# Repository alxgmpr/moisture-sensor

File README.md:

# moisture-sensor

A CR2032-powered Bluetooth soil-moisture sensor with two capacitive sensing zones. An FDC1004 capacitance-to-digital converter measures the probe, an Ezurio BL54L15 (nRF54L15) broadcasts BTHome v2 readings for Home Assistant, and an SHT40 adds temperature and humidity. Configuration and firmware updates happen over BLE.

**Status:** experimental prototype, firmware 0.2.28. SENSE2 shows a weaker response in soil than SENSE1 ([investigation](docs/sense2-investigation-2026-09-25.md)). Moisture percentages are relative to provisional dry/wet endpoints, and battery life and soil accuracy are not yet characterized.

## How it differs

**Y** = included in the device; **N** = not included. Connectivity reflects stock firmware (the BLE sample for b-parasite); other firmware or an external host can add capabilities.

| Feature | This project | [Seeed XIAO](https://wiki.seeedstudio.com/xiao_soil_moisture_sensor/) | [Adafruit STEMMA](https://www.adafruit.com/product/4026) | [Chirp!](https://wemakethings.net/chirp/) | [b-parasite](https://github.com/rbaron/b-parasite) |
| --- | :---: | :---: | :---: | :---: | :---: |
| Capacitive soil sensing | Y | Y | Y | Y | Y |
| Two independently read soil-sensing zones | Y | N | N | N | N |
| Dedicated capacitance-to-digital converter IC | Y | N | N | N | N |
| Operates without an additional controller | Y | Y | N | Y | Y |
| BLE moisture broadcasting in supplied firmware | Y | N | N | N | Y |
| Wi-Fi reporting in supplied firmware | N | Y | N | N | N |
| Onboard coin-cell power support | Y | N | N | Y | Y |
| Onboard AA battery power support | N | Y | N | N | N |
| Relative humidity measurement | Y | N | N | N | Y |
| Audible watering alarm | N | N | N | Y | N |

## Block diagram

```mermaid
flowchart LR
    BAT[CR2032] --> PMIC[nPM2100<br/>power management]
    PMIC --> MCU[BL54L15<br/>nRF54L15 + BLE]
    PMIC -- switched rail --> FDC[FDC1004<br/>capacitance-to-digital]
    FDC -- SENSE1 --- P1[Soil zone 1]
    FDC -- SENSE2 --- P2[Soil zone 2]
    FDC -- I²C --> MCU
    SHT[SHT40<br/>temp / humidity] -- I²C --> MCU
    MCU -- BTHome v2 / SMP --> HA[Home Assistant<br/>Web Bluetooth dashboard]
```

## Build

### Hardware

Open [nrf-moisture-sensor.kicad_pro](nrf-moisture-sensor.kicad_pro) in KiCad. The maintained schematic and PCB are authoritative. See the [BOM](BOM.md) and [design rationale](HARDWARE.md).

### Firmware

Requires Nordic nRF Connect SDK v3.2.2. From the repository root, in an SDK-configured environment:

```sh
west build --sysbuild -p always -b bl54l15_dvk/nrf54l15/cpuapp \
  -d firmware/sensor/build firmware/sensor
sh firmware/sensor/tests/run.sh
```

Wiring, signing, OTA, and SWD recovery are in the [sensor firmware guide](firmware/sensor/README.md). The SDK signing key is for development only.

### Browser configuration

```sh
node firmware/sensor/dashboard/serve.mjs
```

Open <http://127.0.0.1:8766> in Chrome or Edge. Connect during the sensor's advertising window, or use **Explore with demo data** without hardware. See the [dashboard guide](firmware/sensor/dashboard/README.md).

## Notes

Investigation records are in [docs/](docs/).

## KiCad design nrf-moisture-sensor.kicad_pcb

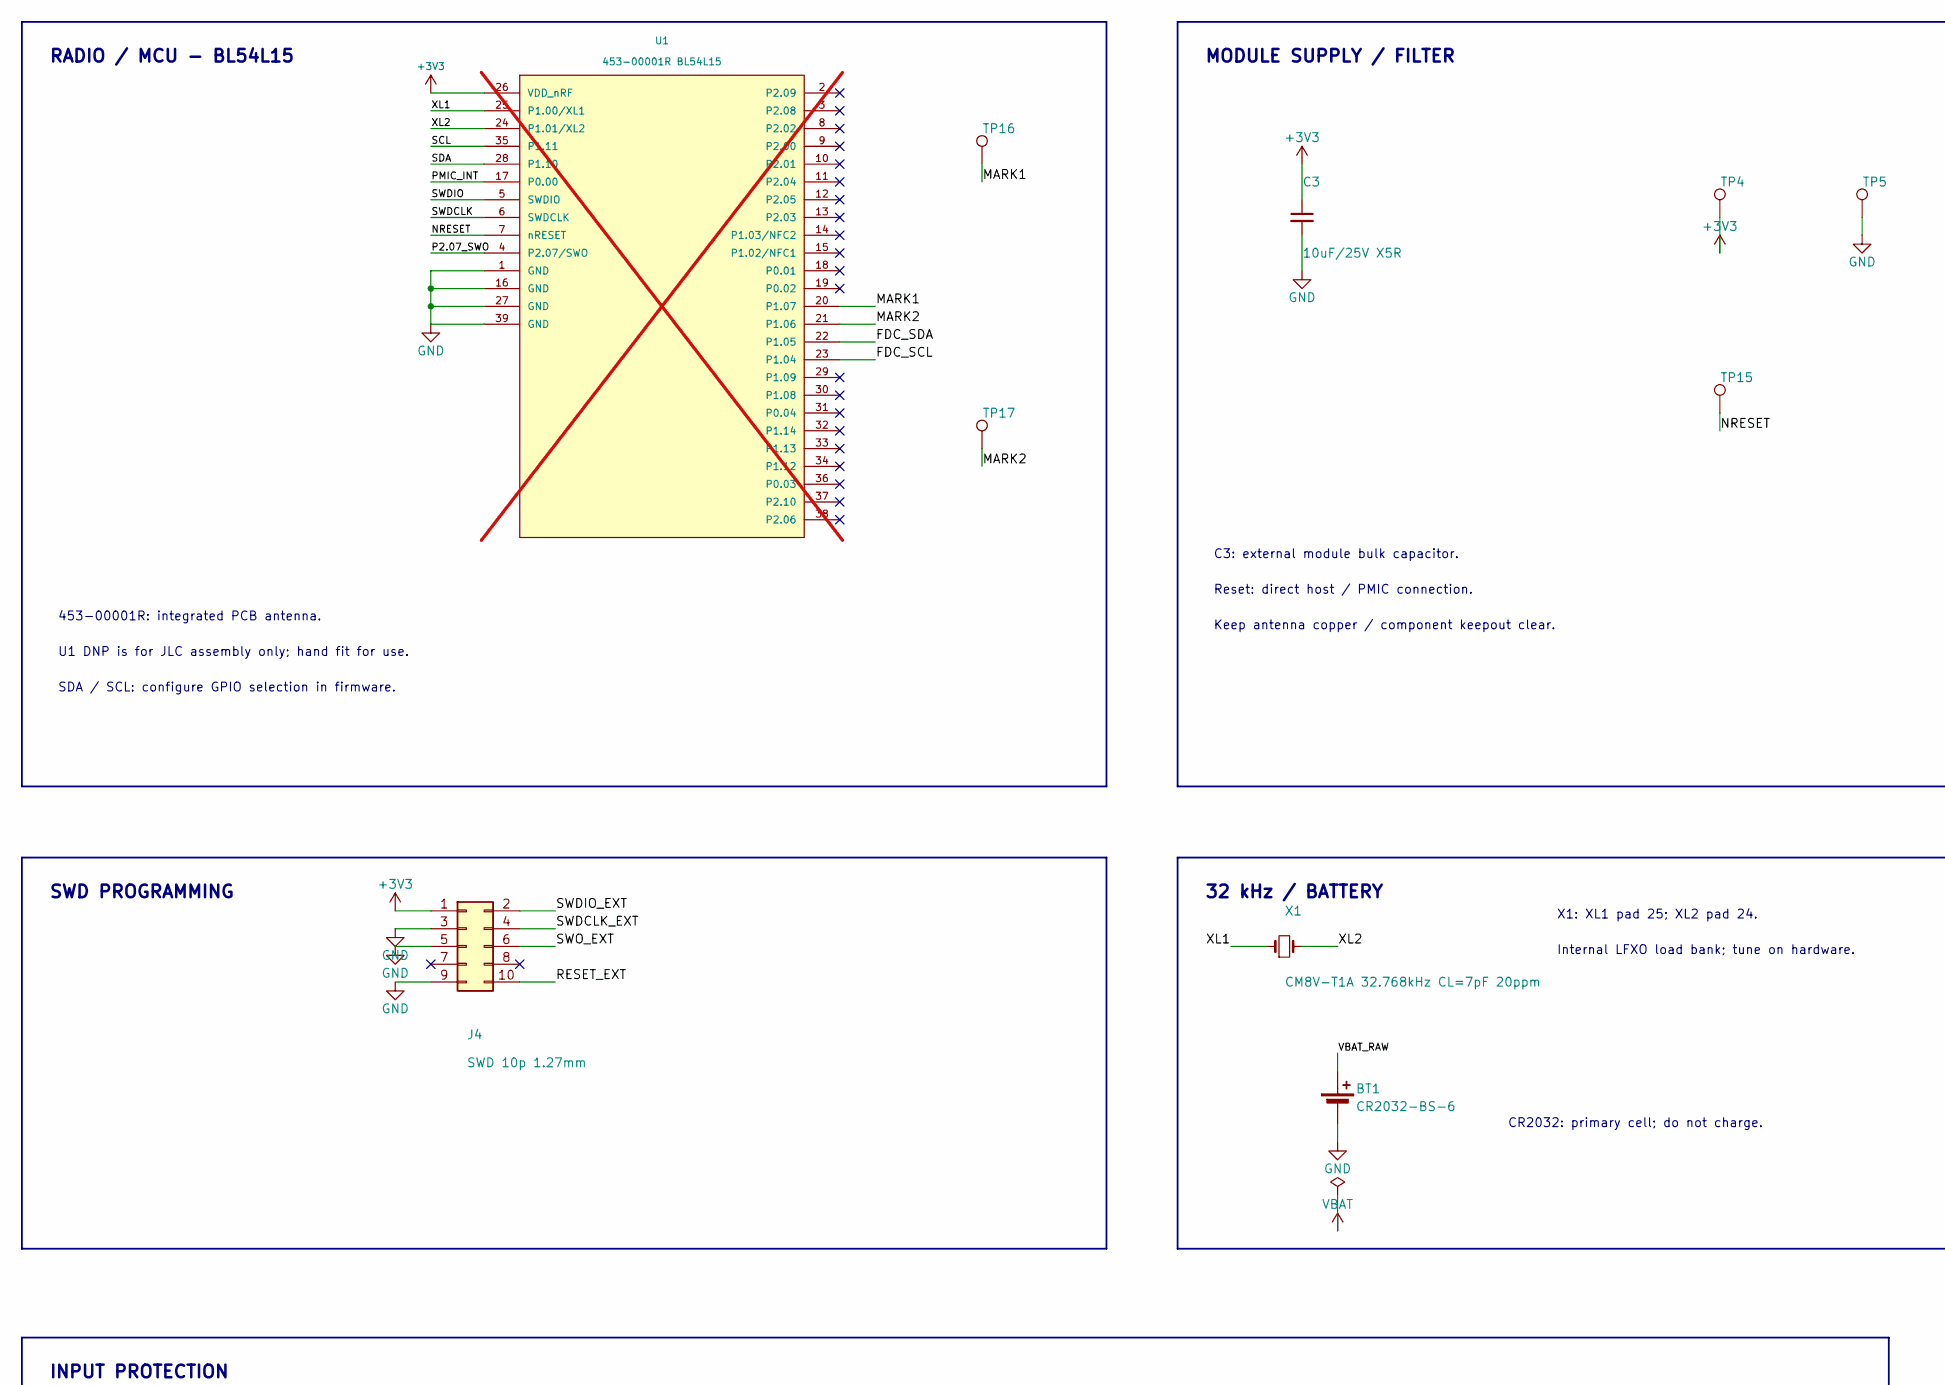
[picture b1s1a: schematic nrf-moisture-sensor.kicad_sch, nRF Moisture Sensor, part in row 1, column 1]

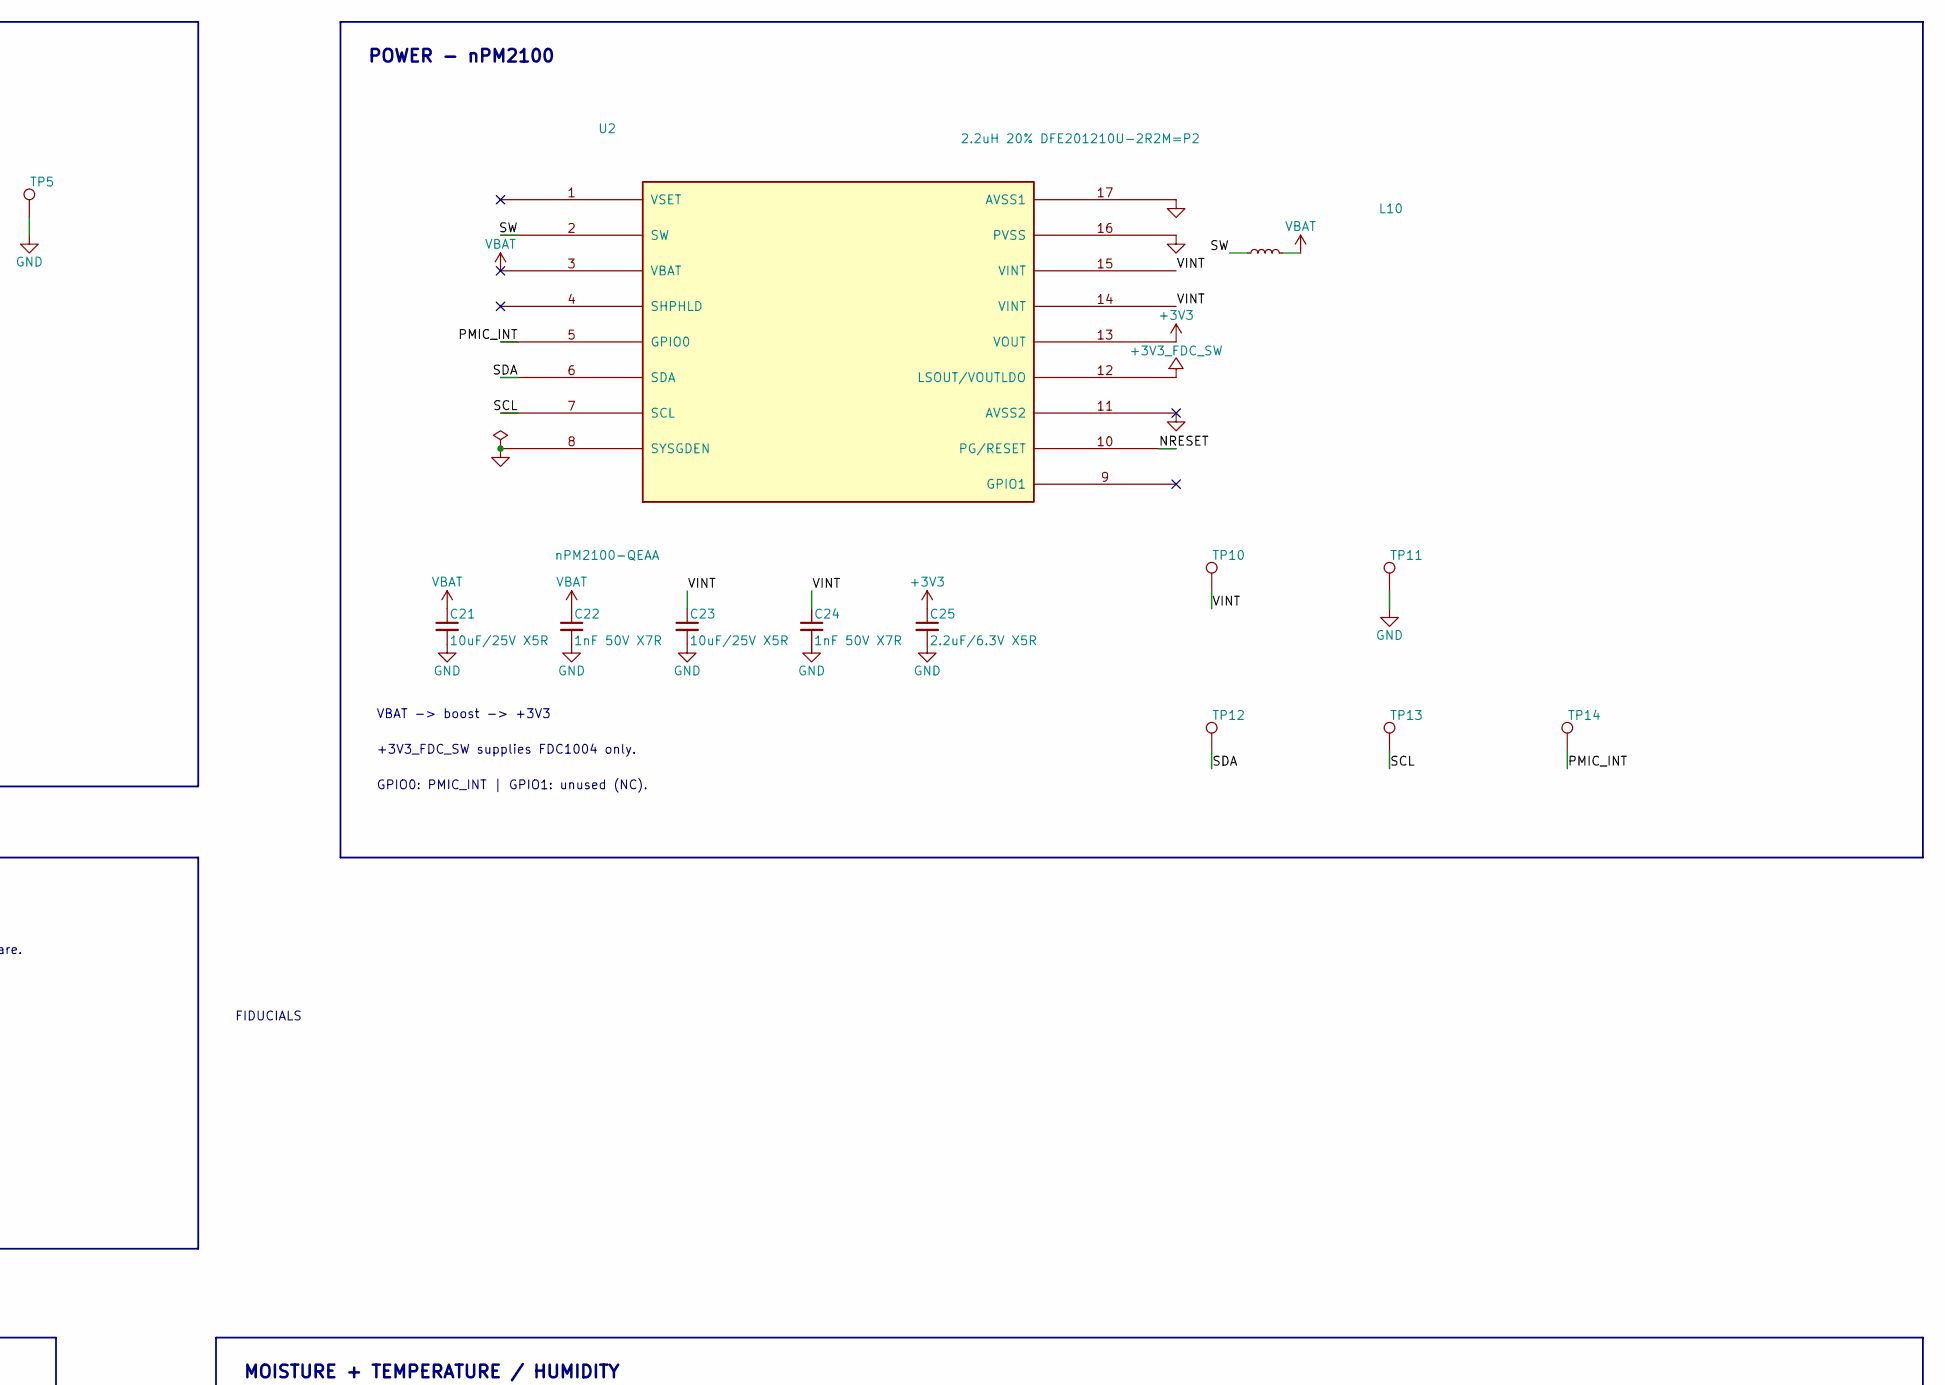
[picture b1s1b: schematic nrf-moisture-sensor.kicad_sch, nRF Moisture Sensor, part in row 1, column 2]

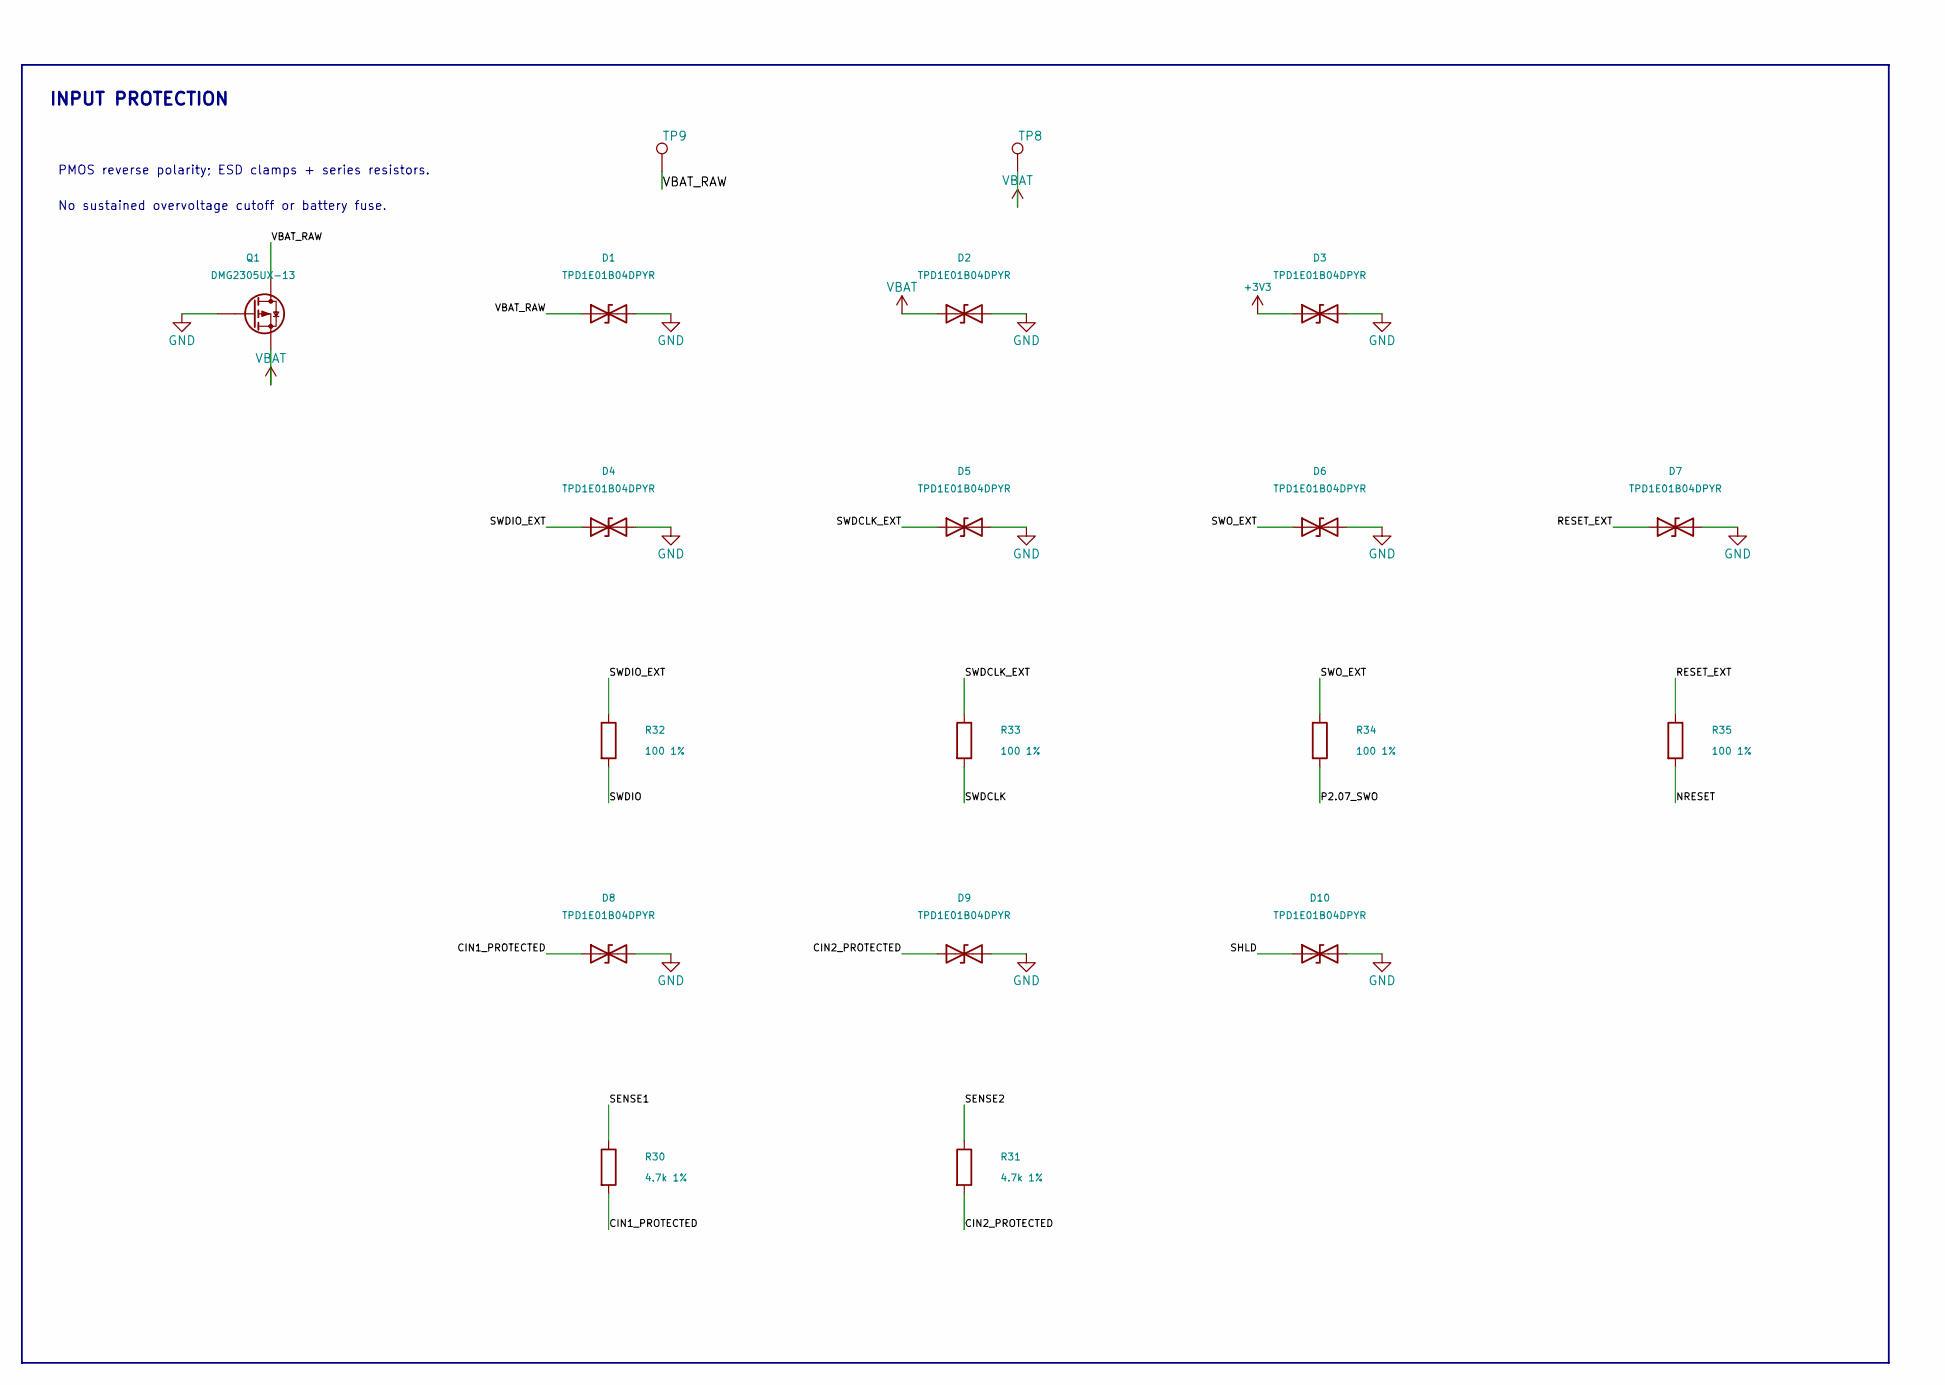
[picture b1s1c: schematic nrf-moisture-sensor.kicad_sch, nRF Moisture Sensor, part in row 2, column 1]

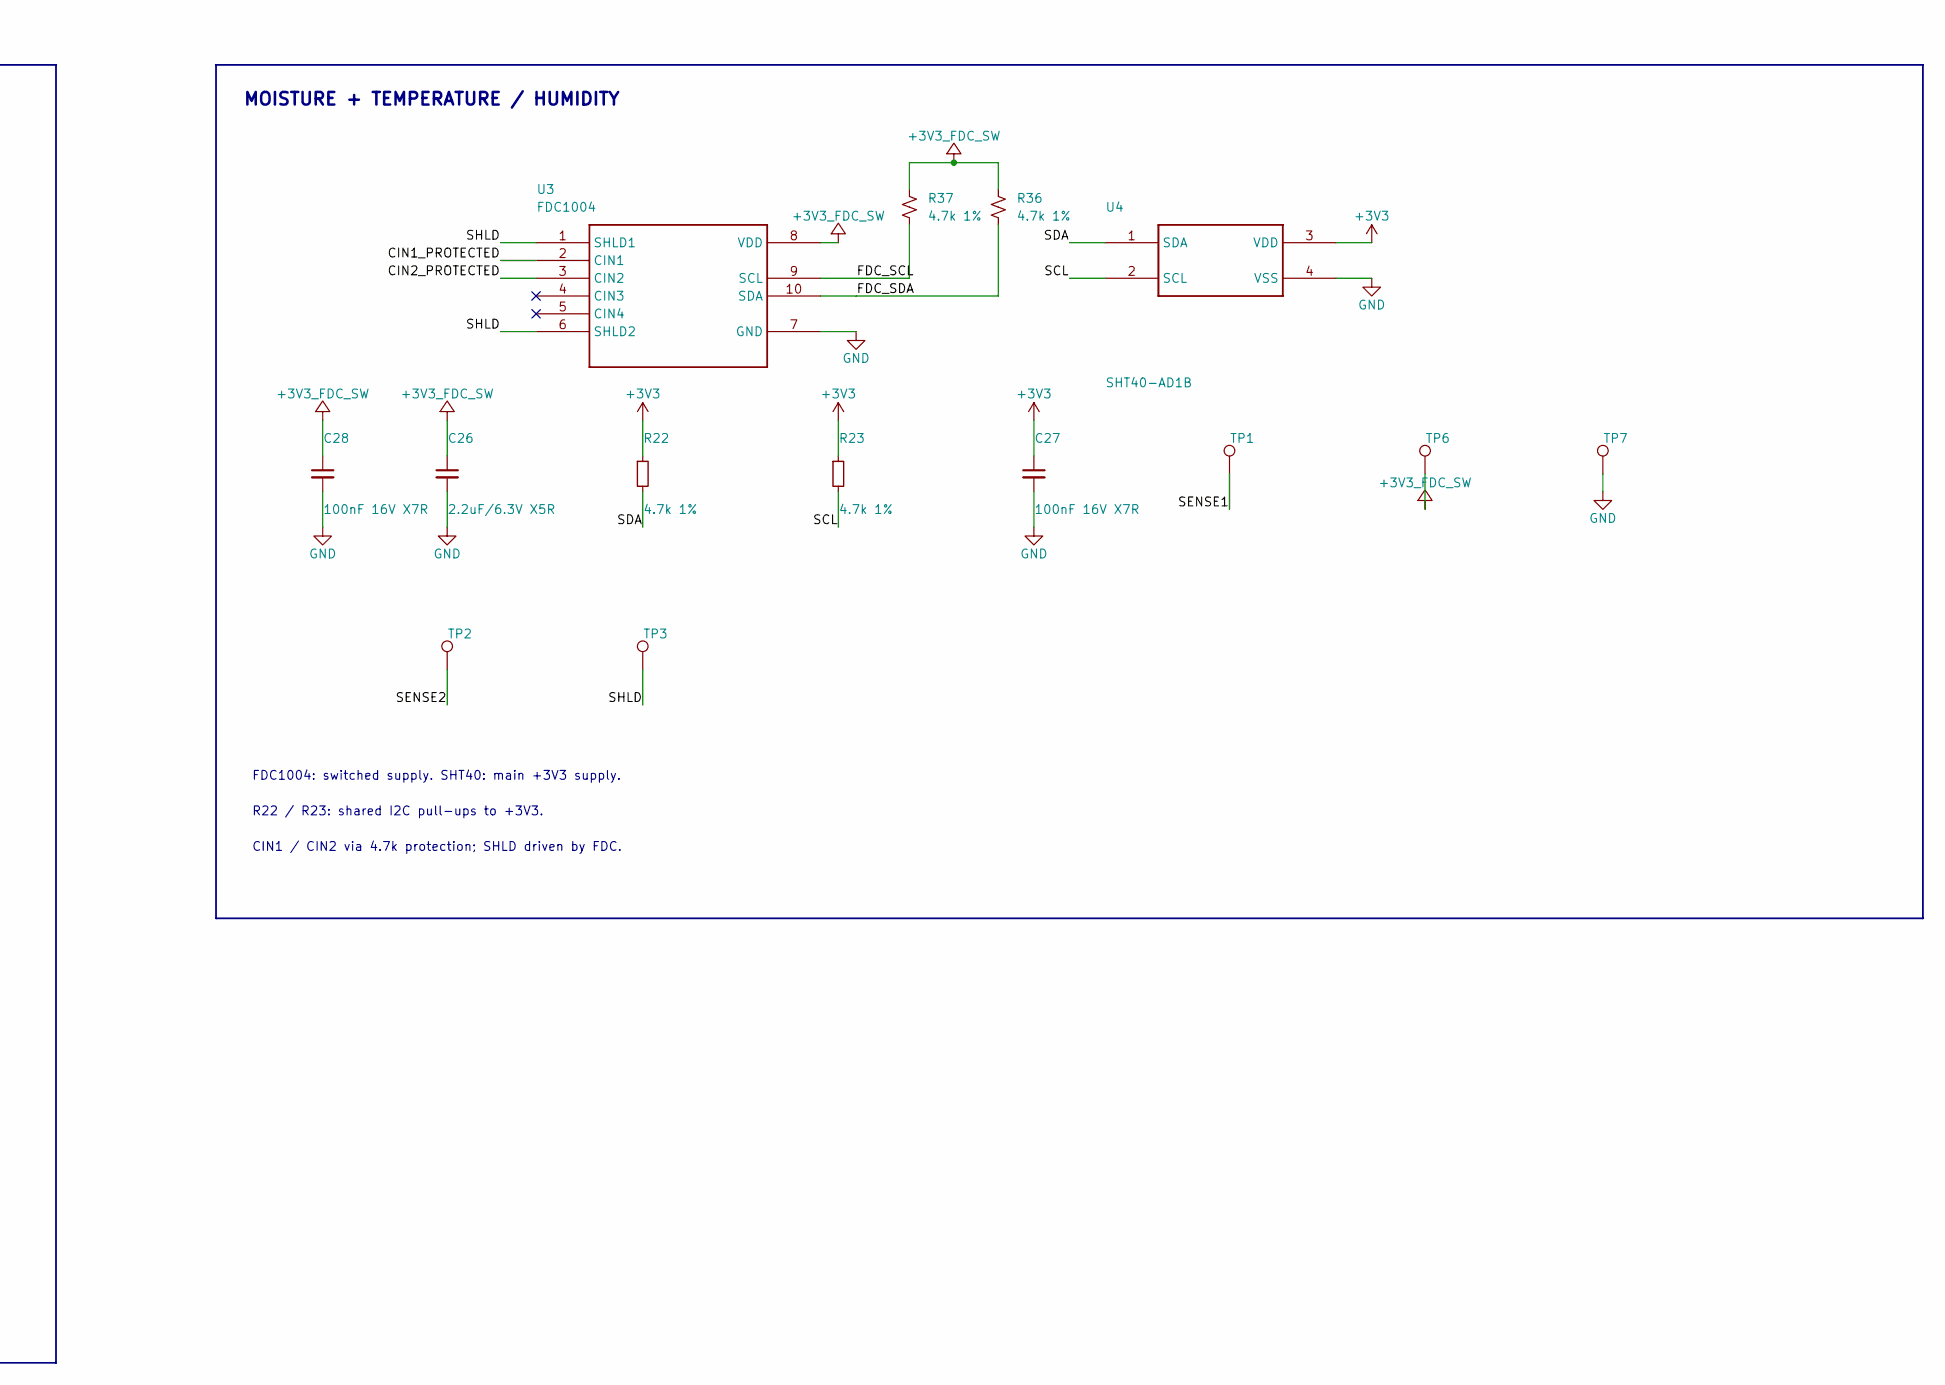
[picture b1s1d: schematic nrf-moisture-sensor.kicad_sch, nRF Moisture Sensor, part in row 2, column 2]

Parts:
BT1: CR2032-BS-6; BatteryHolder_LianXin_CR2032-BS-6; MPN CR2032-BS-6; LCSC C22363833
C3, C21, C23: 10uF/25V X5R; C_0603_1608Metric; MPN CL10A106MA8NRNC; LCSC C96446
C22, C24: 1nF 50V X7R; C_0402_1005Metric; MPN 0402B102K500NT; LCSC C1523
C25, C26: 2.2uF/6.3V X5R; C_0402_1005Metric; MPN CL05A225MQ5NSNC; LCSC C12530
C27, C28: 100nF 16V X7R; C_0402_1005Metric; MPN CL05B104KO5NNNC; LCSC C1525
D1, D2, D3, D4, D5, D6, D7, D8, D9, D10: TPD1E01B04DPYR; Texas_DPY0002A_0.6x1mm_P0.65mm; MPN TPD1E01B04DPYR; LCSC C779389
J4: SWD 10p 1.27mm; Tag-Connect_TC2050-IDC-NL_2x05_P1.27mm_Vertical
L10: 2.2uH 20% DFE201210U-2R2M=P2; IND_Murata_DFE201210U; MPN DFE201210U-2R2M=P2; LCSC C2049745
Q1: DMG2305UX-13; SOT-23; MPN DMG2305UX-13; LCSC C144153
R22, R23, R30, R31, R36, R37: 4.7k 1%; R_0402_1005Metric; MPN 0402WGF4701TCE; LCSC C25900
R32, R33, R34, R35: 100 1%; R_0402_1005Metric; MPN 0402WGF1000TCE; LCSC C25076
TP1: SENSE1; TestPoint_Pad_D1.0mm
TP2: SENSE2; TestPoint_Pad_D1.0mm
TP3: SHLD; TestPoint_Pad_D1.0mm
TP4: +3V3; TestPoint_Pad_D1.0mm
TP5, TP7, TP11: GND; TestPoint_Pad_D1.0mm
TP6: +3V3_FDC_SW; TestPoint_Pad_D1.0mm
TP8: VBAT; TestPoint_Pad_D1.0mm
TP9: VBAT_RAW; TestPoint_Pad_D1.0mm
TP10: VINT; TestPoint_Pad_D1.0mm
TP12: SDA; TestPoint_Pad_D1.0mm
TP13: SCL; TestPoint_Pad_D1.0mm
TP14: PMIC_INT; TestPoint_Pad_D1.0mm
TP15: NRESET; TestPoint_Pad_D1.0mm
TP16: MARK1; TestPoint_Pad_D1.0mm
TP17: MARK2; TestPoint_Pad_D1.0mm
U1: 453-00001R BL54L15; Ezurio_BL54L15_453-00001; MPN 453-00001R; DigiKey 776-453-00001RCT-ND; not fitted
U2: nPM2100-QEAA; QFN-16-1EP_4x4mm_P0.65mm_EP2.7x2.7mm_ThermalVias; MPN NPM2100-QEAA-R7; LCSC C46968654
U3: FDC1004; MSOP-10_3x3mm_P0.5mm; MPN FDC1004DGSR; LCSC C2865994
U4: SHT40-AD1B; Sensirion_DFN-4_1.5x1.5mm_P0.8mm_SHT4x_NoCentralPad; MPN SHT40-AD1B-R2; LCSC C2909890
X1: CM8V-T1A 32.768kHz CL=7pF 20ppm; XTAL_CM8V-T1A_2012; MPN CM8V-T1A-32.768KHZ-7PF-20PPM-TA-QC; LCSC C5136974

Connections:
+3V3: C3.1, C25.1, C27.1, D3.1 (A1), J4.1, R22.1, R23.1, TP4.1 (1_1), U1.26 (VDD_nRF), U2.13 (VOUT), U4.3 (VDD)
+3V3_FDC_SW: C26.1, C28.1, R36.1, R37.1, TP6.1 (1_1), U2.12 (LSOUT/VOUTLDO), U3.8 (VDD)
/CIN1_PROTECTED: D8.1 (A1), R30.2, U3.2 (CIN1)
/CIN2_PROTECTED: D9.1 (A1), R31.2, U3.3 (CIN2)
/FDC_SCL: R37.2, U1.23 (P1.04), U3.9 (SCL)
/FDC_SDA: R36.2, U1.22 (P1.05), U3.10 (SDA)
/MARK1: TP16.1 (1_1), U1.20 (P1.07)
/MARK2: TP17.1 (1_1), U1.21 (P1.06)
/NRESET: R35.2, TP15.1 (1_1), U1.7 (nRESET), U2.10 (PG/RESET)
/P2.07_SWO: R34.2, U1.4 (P2.07/SWO)
/PMIC_INT: TP14.1 (1_1), U1.17 (P0.00), U2.5 (GPIO0)
/RESET_EXT: D7.1 (A1), J4.10, R35.1
/SCL: R23.2, TP13.1 (1_1), U1.35 (P1.11), U2.7 (SCL), U4.2 (SCL)
/SDA: R22.2, TP12.1 (1_1), U1.28 (P1.10), U2.6 (SDA), U4.1 (SDA)
/SENSE1: R30.1, TP1.1 (1_1)
/SENSE2: R31.1, TP2.1 (1_1)
/SHLD: D10.1 (A1), TP3.1 (1_1), U3.1 (SHLD1), U3.6 (SHLD2)
/SW: L10.1, U2.2 (SW)
/SWDCLK: R33.2, U1.6 (SWDCLK)
/SWDCLK_EXT: D5.1 (A1), J4.4, R33.1
/SWDIO: R32.2, U1.5 (SWDIO)
/SWDIO_EXT: D4.1 (A1), J4.2, R32.1
/SWO_EXT: D6.1 (A1), J4.6, R34.1
/VBAT_RAW: BT1.1 (+), D1.1 (A1), Q1.3 (D), TP9.1 (1_1)
/VINT: C23.1, C24.1, TP10.1 (1_1), U2.14 (VINT), U2.15 (VINT)
/XL1: U1.25 (P1.00/XL1), X1.1
/XL2: U1.24 (P1.01/XL2), X1.2
GND: BT1.2 (-), C3.2, C21.2, C22.2, C23.2, C24.2, C25.2, C26.2, C27.2, C28.2, D1.2 (A2), D2.2 (A2), D3.2 (A2), D4.2 (A2), D5.2 (A2), D6.2 (A2), D7.2 (A2), D8.2 (A2), D9.2 (A2), D10.2 (A2), J4.3, J4.5, J4.9, Q1.1 (G), TP5.1 (1_1), TP7.1 (1_1), TP11.1 (1_1), U1.1 (GND), U1.16 (GND), U1.27 (GND), U1.39 (GND), U2.8 (SYSGDEN), U2.11 (AVSS2), U2.16 (PVSS), U2.17 (AVSS1), U3.7 (GND), U4.4 (VSS)
VBAT: C21.1, C22.1, D2.1 (A1), L10.2, Q1.2 (S), TP8.1 (1_1), U2.3 (VBAT)

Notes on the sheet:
RADIO / MCU - BL54L15
MODULE SUPPLY / FILTER
SWD PROGRAMMING
32 kHz / BATTERY
POWER - nPM2100
INPUT PROTECTION
MOISTURE + TEMPERATURE / HUMIDITY
453-00001R: integrated PCB antenna.
U1 DNP is for JLC assembly only; hand fit for use.
SDA / SCL: configure GPIO selection in firmware.
C3: external module bulk capacitor.
Reset: direct host / PMIC connection.
Keep antenna copper / component keepout clear.
X1: XL1 pad 25; XL2 pad 24.
Internal LFXO load bank; tune on hardware.
CR2032: primary cell; do not charge.
VBAT -> boost -> +3V3
+3V3_FDC_SW supplies FDC1004 only.
GPIO0: PMIC_INT | GPIO1: unused (NC).
PMOS reverse polarity; ESD clamps + series resistors.
No sustained overvoltage cutoff or battery fuse.
FDC1004: switched supply. SHT40: main +3V3 supply.
R22 / R23: shared I2C pull-ups to +3V3.
CIN1 / CIN2 via 4.7k protection; SHLD driven by FDC.
FIDUCIALS

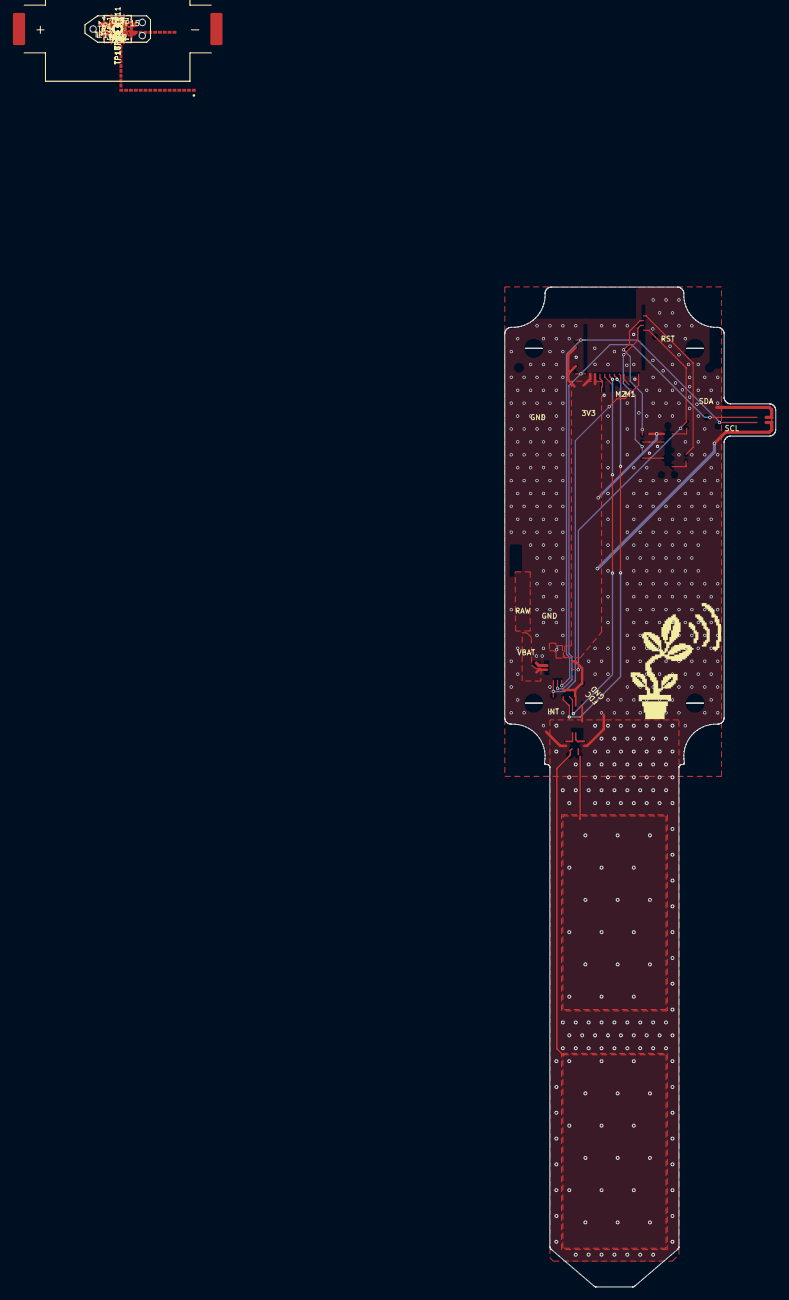
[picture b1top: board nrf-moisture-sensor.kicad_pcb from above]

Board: 4 copper layers, 42.0 x 155.0 mm, 58 parts (1 on the bottom side), 29 nets.

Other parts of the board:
TH1, TH2, TH3: ToolingHole_JLC_1.152mm

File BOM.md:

> Rev A checkpoint: consolidated schematic and updated PCB match the JLC export. See [checkpoint and Rev B follow-ups](docs/rev-a-checkpoint/README.md).

# nRF Moisture Sensor — Bill of Materials

Generated from the maintained schematic on 2026-09-09 using KiCad's BOM exporter.
The [source CSV](docs/schematic-consolidation-2026-09-09/Product-BOM.csv) includes manufacturer and assembly-stage DNP fields.
This supersedes the earlier manually maintained selection table; historical selections remain in Git.

U1 is required in the finished product but marked DNP for the JLC assembly stage and fitted separately.
The CR2032 cell is not included as a schematic component. Bare PCB features are excluded from purchasing.
No stock, price, or fabrication approval is implied by this export.

| Ref | Value | Footprint | MPN | Manufacturer | LCSC | JLC DNP |
| --- | --- | --- | --- | --- | --- | --- |
| BT1 | CR2032-BS-6 | footprints:BatteryHolder_LianXin_CR2032-BS-6 | CR2032-BS-6 | Lian Xin Technology | C22363833 |  |
| C3 | 10uF/25V X5R | Capacitor_SMD:C_0603_1608Metric | CL10A106MA8NRNC | Samsung | C96446 |  |
| C21 | 10uF/25V X5R | Capacitor_SMD:C_0603_1608Metric | CL10A106MA8NRNC | Samsung | C96446 |  |
| C22 | 1nF 50V X7R | Capacitor_SMD:C_0402_1005Metric | 0402B102K500NT | FH | C1523 |  |
| C23 | 10uF/25V X5R | Capacitor_SMD:C_0603_1608Metric | CL10A106MA8NRNC | Samsung | C96446 |  |
| C24 | 1nF 50V X7R | Capacitor_SMD:C_0402_1005Metric | 0402B102K500NT | FH | C1523 |  |
| C25 | 2.2uF/6.3V X5R | Capacitor_SMD:C_0402_1005Metric | CL05A225MQ5NSNC | Samsung | C12530 |  |
| C26 | 2.2uF/6.3V X5R | Capacitor_SMD:C_0402_1005Metric | CL05A225MQ5NSNC | Samsung | C12530 |  |
| C27 | 100nF 16V X7R | Capacitor_SMD:C_0402_1005Metric | CL05B104KO5NNNC | Samsung | C1525 |  |
| C28 | 100nF 16V X7R | Capacitor_SMD:C_0402_1005Metric | CL05B104KO5NNNC | Samsung | C1525 |  |
| D1 | TPD1E01B04DPYR | Package_SON:Texas_DPY0002A_0.6x1mm_P0.65mm | TPD1E01B04DPYR | Texas Instruments | C779389 |  |
| D2 | TPD1E01B04DPYR | Package_SON:Texas_DPY0002A_0.6x1mm_P0.65mm | TPD1E01B04DPYR | Texas Instruments | C779389 |  |
| D3 | TPD1E01B04DPYR | Package_SON:Texas_DPY0002A_0.6x1mm_P0.65mm | TPD1E01B04DPYR | Texas Instruments | C779389 |  |
| D4 | TPD1E01B04DPYR | Package_SON:Texas_DPY0002A_0.6x1mm_P0.65mm | TPD1E01B04DPYR | Texas Instruments | C779389 |  |
| D5 | TPD1E01B04DPYR | Package_SON:Texas_DPY0002A_0.6x1mm_P0.65mm | TPD1E01B04DPYR | Texas Instruments | C779389 |  |
| D6 | TPD1E01B04DPYR | Package_SON:Texas_DPY0002A_0.6x1mm_P0.65mm | TPD1E01B04DPYR | Texas Instruments | C779389 |  |
| D7 | TPD1E01B04DPYR | Package_SON:Texas_DPY0002A_0.6x1mm_P0.65mm | TPD1E01B04DPYR | Texas Instruments | C779389 |  |
| D8 | TPD1E01B04DPYR | Package_SON:Texas_DPY0002A_0.6x1mm_P0.65mm | TPD1E01B04DPYR | Texas Instruments | C779389 |  |
| D9 | TPD1E01B04DPYR | Package_SON:Texas_DPY0002A_0.6x1mm_P0.65mm | TPD1E01B04DPYR | Texas Instruments | C779389 |  |
| D10 | TPD1E01B04DPYR | Package_SON:Texas_DPY0002A_0.6x1mm_P0.65mm | TPD1E01B04DPYR | Texas Instruments | C779389 |  |
| L10 | 2.2uH 20% DFE201210U-2R2M=P2 | footprints:IND_Murata_DFE201210U | DFE201210U-2R2M=P2 | Murata | C2049745 |  |
| Q1 | DMG2305UX-13 | Package_TO_SOT_SMD:SOT-23 | DMG2305UX-13 | Diodes Incorporated | C144153 |  |
| R22 | 4.7k 1% | Resistor_SMD:R_0402_1005Metric | 0402WGF4701TCE | UNI-ROYAL | C25900 |  |
| R23 | 4.7k 1% | Resistor_SMD:R_0402_1005Metric | 0402WGF4701TCE | UNI-ROYAL | C25900 |  |
| R30 | 4.7k 1% | Resistor_SMD:R_0402_1005Metric | 0402WGF4701TCE | UNI-ROYAL | C25900 |  |
| R31 | 4.7k 1% | Resistor_SMD:R_0402_1005Metric | 0402WGF4701TCE | UNI-ROYAL | C25900 |  |
| R32 | 100 1% | Resistor_SMD:R_0402_1005Metric | 0402WGF1000TCE | UNI-ROYAL | C25076 |  |
| R33 | 100 1% | Resistor_SMD:R_0402_1005Metric | 0402WGF1000TCE | UNI-ROYAL | C25076 |  |
| R34 | 100 1% | Resistor_SMD:R_0402_1005Metric | 0402WGF1000TCE | UNI-ROYAL | C25076 |  |
| R35 | 100 1% | Resistor_SMD:R_0402_1005Metric | 0402WGF1000TCE | UNI-ROYAL | C25076 |  |
| R36 | 4.7k 1% | Resistor_SMD:R_0402_1005Metric | 0402WGF4701TCE | UNI-ROYAL | C25900 |  |
| R37 | 4.7k 1% | Resistor_SMD:R_0402_1005Metric | 0402WGF4701TCE | UNI-ROYAL | C25900 |  |
| U1 | 453-00001R BL54L15 | footprints:Ezurio_BL54L15_453-00001 | 453-00001R | Ezurio |  | DNP |
| U2 | nPM2100-QEAA | Package_DFN_QFN:QFN-16-1EP_4x4mm_P0.65mm_EP2.7x2.7mm_ThermalVias | NPM2100-QEAA-R7 | Nordic Semiconductor | C46968654 |  |
| U3 | FDC1004 | Package_SO:MSOP-10_3x3mm_P0.5mm | FDC1004DGSR | Texas Instruments | C2865994 |  |
| U4 | SHT40-AD1B | Sensor_Humidity:Sensirion_DFN-4_1.5x1.5mm_P0.8mm_SHT4x_NoCentralPad | SHT40-AD1B-R2 | Sensirion | C2909890 |  |
| X1 | CM8V-T1A 32.768kHz CL=7pF 20ppm | footprints:XTAL_CM8V-T1A_2012 | CM8V-T1A-32.768KHZ-7PF-20PPM-TA-QC | Micro Crystal | C5136974 |  |

All resistors and capacitors use standard KiCad reflow footprints. D1–D10 use
`Package_SON:Texas_DPY0002A_0.6x1mm_P0.65mm`. The module, crystal, inductor,
and battery holder retain their verified part-specific footprints.

## Qualification items

- C21/C23 now use CL10A106MA8NRNC, 10 µF 0603. Verify ≥3.5 µF effective over actual VBAT/VINT bias, temperature, tolerance and aging; these are development selections, not newly qualified capacitors.
- Qualification and current firmware: [reliability work](docs/reliability-2026-09-07/README.md).
- VOUT: C3 + C25 + C27 total 12.3 µF nominal, before module loading. Check both 0.7 µF minimum and 15 µF maximum effective limits. LDOSW draws from VINT; C26/C28 do not directly add to VOUT.
- C26/C27/C28 are now selected in the schematic as listed above; earlier TBD and 0201 descriptions were stale.
- Preserve the exact BL54L15 antenna module, SHT40-AD1B opening (no integrated membrane), inductor footprint, and X1 load/drive requirements. Keep the cell out during hot work.
- Qualify module supply ripple and low-battery radio/heater transients before release.

See the [component review](docs/component-review-2026-09-05/README.md) and [power review](docs/power-review-2026-09-05/README.md) for evidence and test procedures.

Current schematic revision implements the consolidated development BOM. PCB update and layout are assigned to Alex. See [implementation record](docs/schematic-consolidation-2026-09-09/README.md); older cost-review selections are historical.
